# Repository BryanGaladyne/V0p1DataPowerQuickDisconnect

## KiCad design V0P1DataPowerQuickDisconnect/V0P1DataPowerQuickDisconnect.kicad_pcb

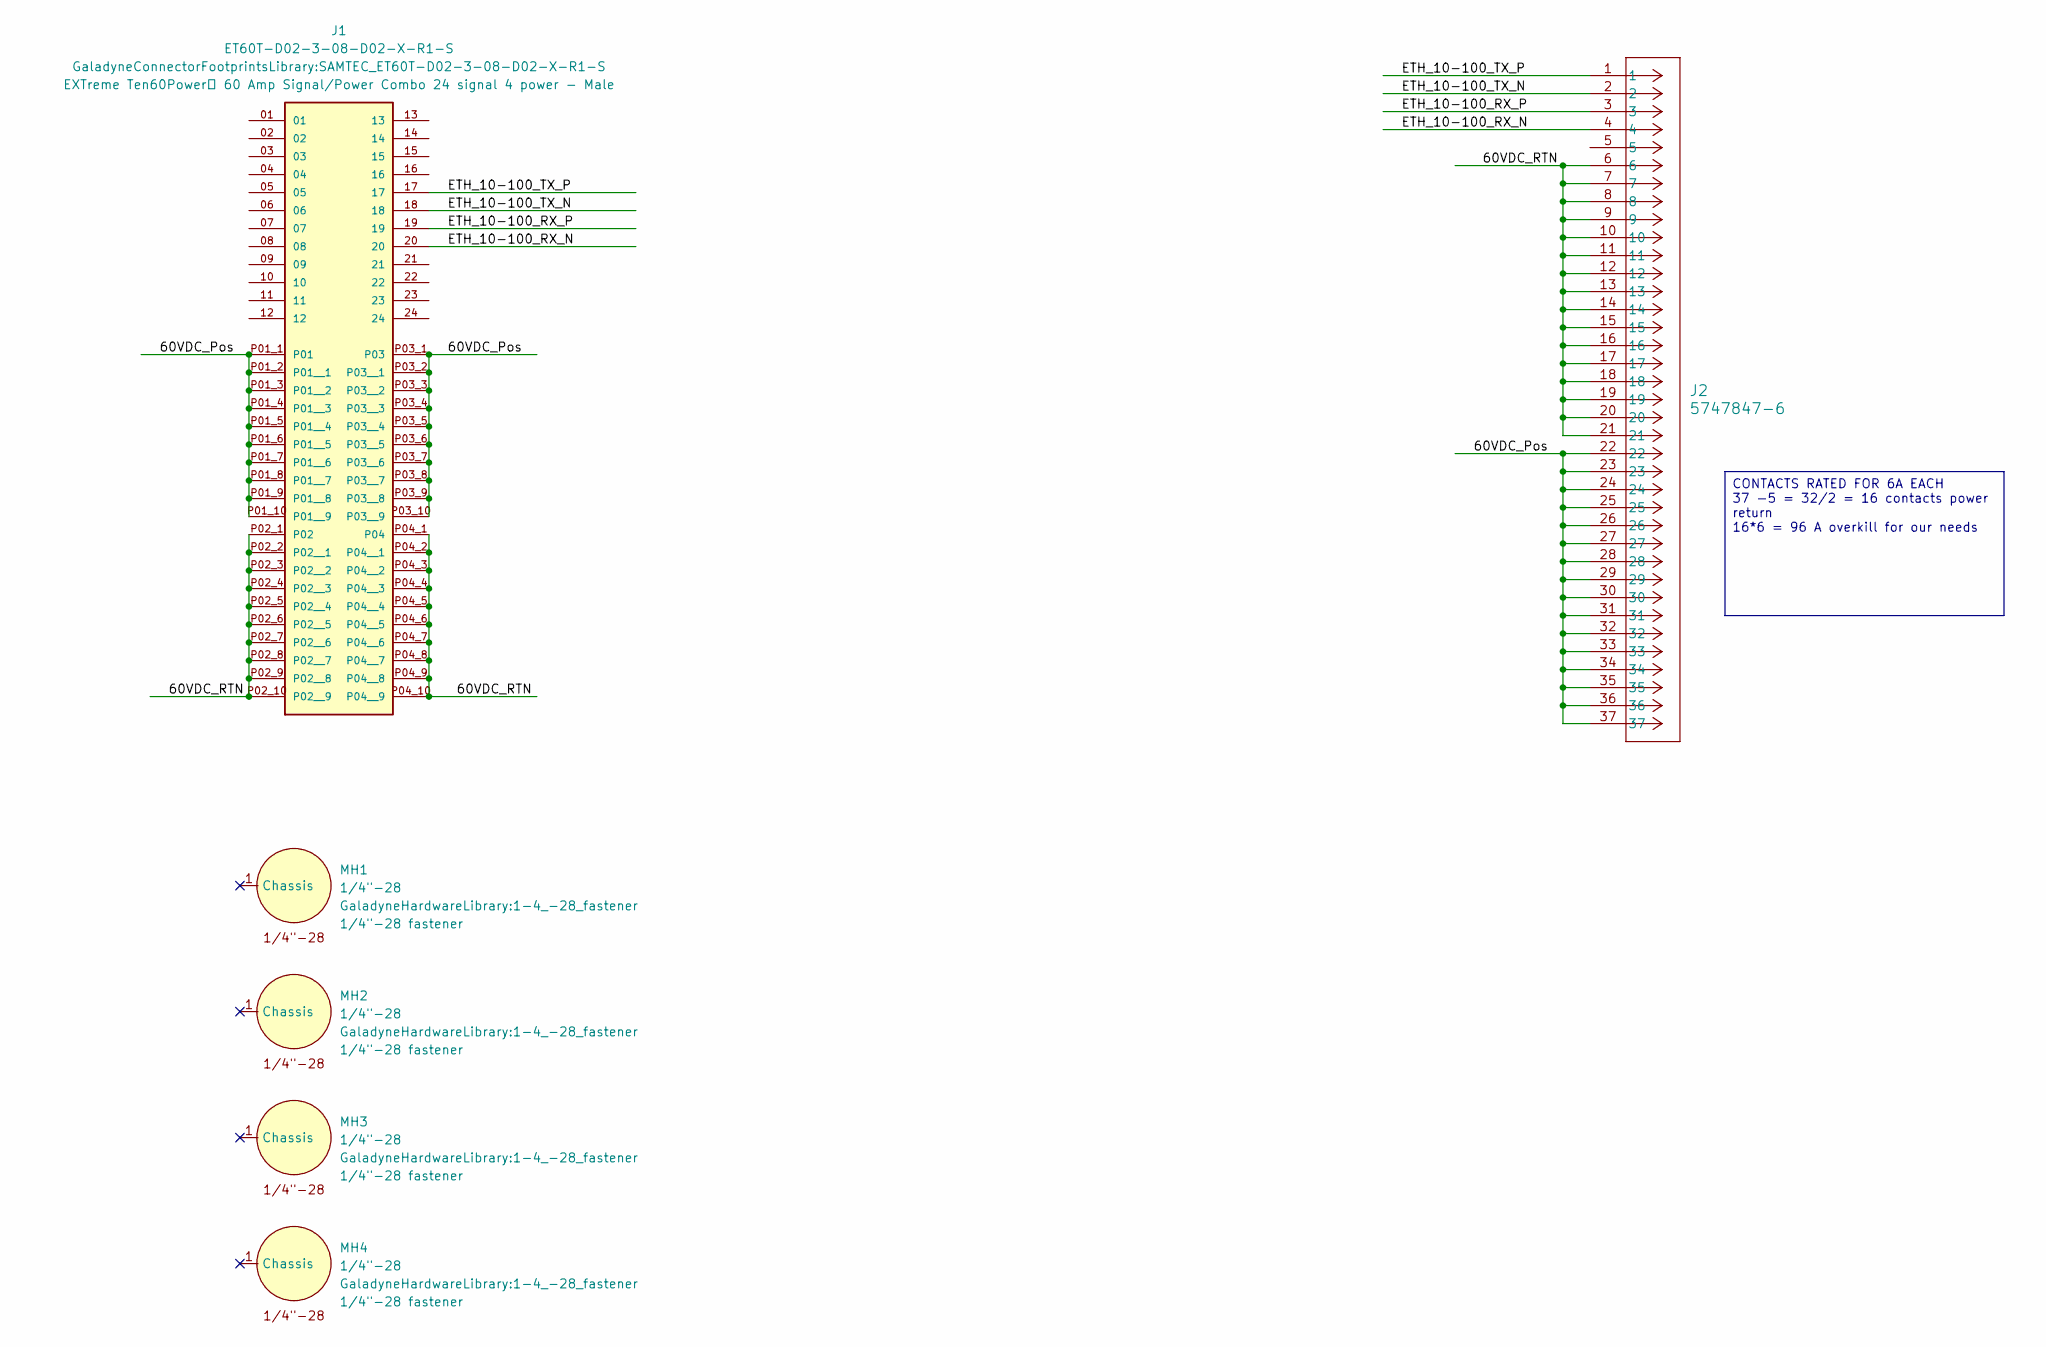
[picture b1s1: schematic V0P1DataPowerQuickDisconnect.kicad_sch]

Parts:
J1: ET60T-D02-3-08-D02-X-R1-S; SAMTEC_ET60T-D02-3-08-D02-X-R1-S
J2: 5747847-6; CONN_5747847-6_TYC; MPN 5747847-6
MH1, MH2, MH3, MH4: 1/4"-28; 1-4_-28_fastener

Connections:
/60VDC_Pos: J1.P01_1 (P01), J1.P01_2 (P01__1), J1.P01_3 (P01__2), J1.P01_4 (P01__3), J1.P01_5 (P01__4), J1.P01_6 (P01__5), J1.P01_7 (P01__6), J1.P01_8 (P01__7), J1.P01_9 (P01__8), J1.P01_10 (P01__9), J1.P03_1 (P03), J1.P03_2 (P03__1), J1.P03_3 (P03__2), J1.P03_4 (P03__3), J1.P03_5 (P03__4), J1.P03_6 (P03__5), J1.P03_7 (P03__6), J1.P03_8 (P03__7), J1.P03_9 (P03__8), J1.P03_10 (P03__9), J2.22, J2.23, J2.24, J2.25, J2.26, J2.27, J2.28, J2.29, J2.30, J2.31, J2.32, J2.33, J2.34, J2.35, J2.36, J2.37
/60VDC_RTN: J1.P02_1 (P02), J1.P02_2 (P02__1), J1.P02_3 (P02__2), J1.P02_4 (P02__3), J1.P02_5 (P02__4), J1.P02_6 (P02__5), J1.P02_7 (P02__6), J1.P02_8 (P02__7), J1.P02_9 (P02__8), J1.P02_10 (P02__9), J1.P04_1 (P04), J1.P04_2 (P04__1), J1.P04_3 (P04__2), J1.P04_4 (P04__3), J1.P04_5 (P04__4), J1.P04_6 (P04__5), J1.P04_7 (P04__6), J1.P04_8 (P04__7), J1.P04_9 (P04__8), J1.P04_10 (P04__9), J2.6, J2.7, J2.8, J2.9, J2.10, J2.11, J2.12, J2.13, J2.14, J2.15, J2.16, J2.17, J2.18, J2.19, J2.20, J2.21
/ETH_10-100_RX_N: J1.20, J2.4
/ETH_10-100_RX_P: J1.19, J2.3
/ETH_10-100_TX_N: J1.18, J2.2
/ETH_10-100_TX_P: J1.17, J2.1

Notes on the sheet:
CONTACTS RATED FOR 6A EACH 37 -5 = 32/2 = 16 contacts power return 16*6 = 96 A overkill for our needs

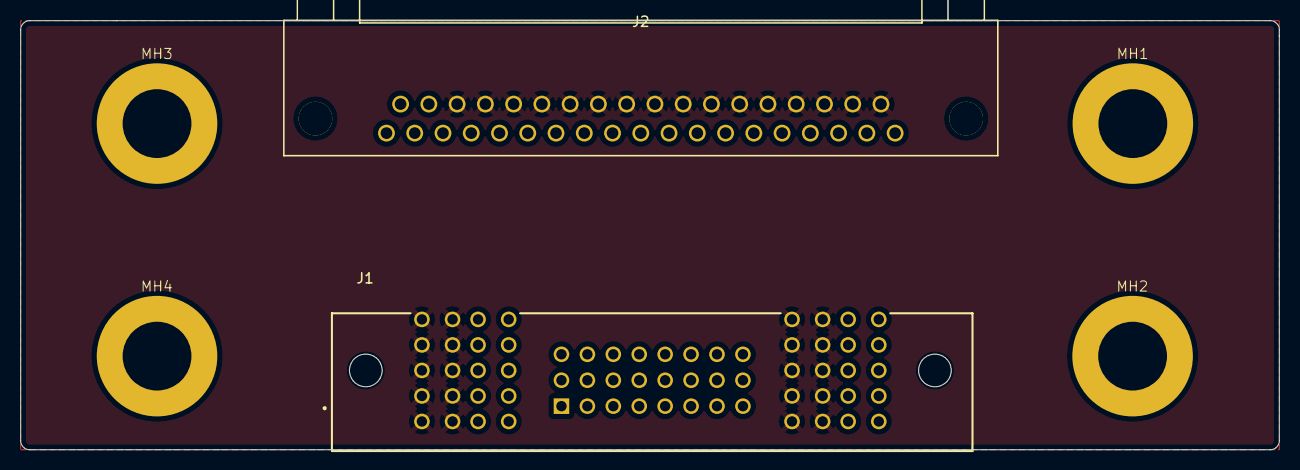
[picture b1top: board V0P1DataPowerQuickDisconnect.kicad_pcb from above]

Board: 4 copper layers, 123.3 x 42.0 mm, 6 parts (0 on the bottom side), 6 nets.

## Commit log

2026-04-10 fill zones, add step files
